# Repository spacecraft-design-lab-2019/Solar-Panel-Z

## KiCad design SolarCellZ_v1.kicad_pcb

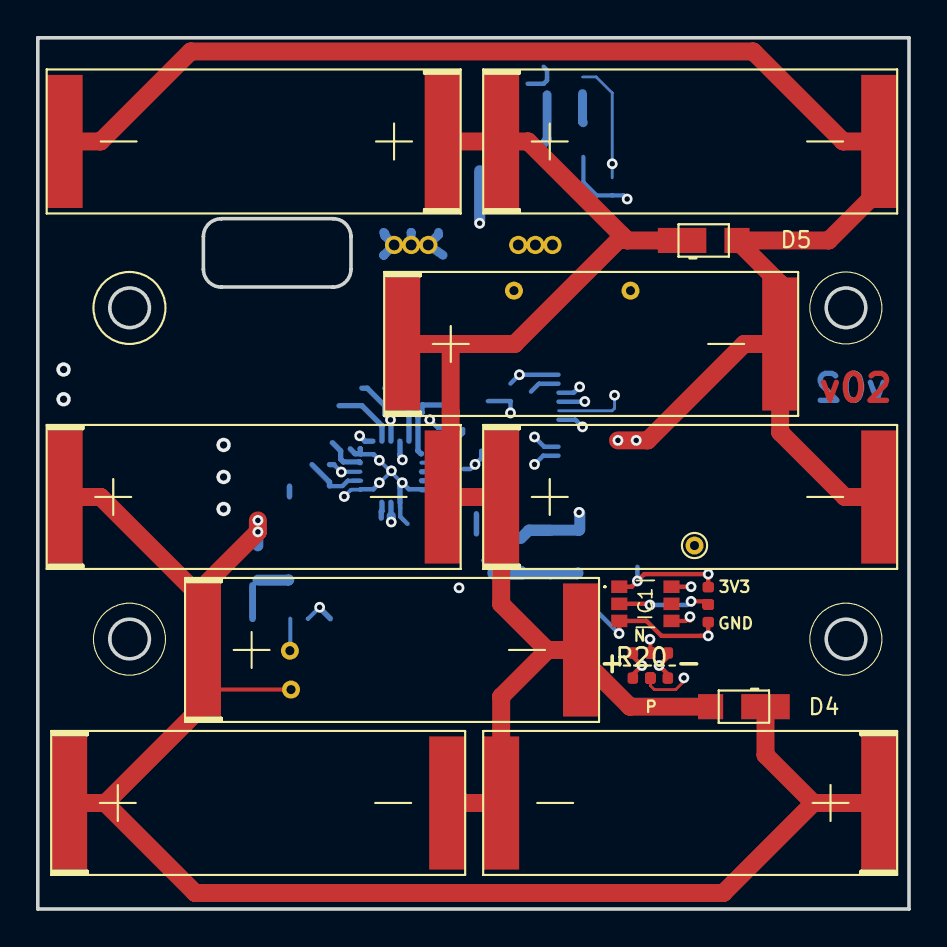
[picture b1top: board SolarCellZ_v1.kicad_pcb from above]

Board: 6 copper layers, 48.4 x 48.4 mm, 62 parts (0 on the bottom side), 31 nets.

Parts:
C1: 1.0uF; C_0402_1005Metric
C2, C5, C9, C10, C13: 0.1uF; C_0402_1005Metric
C3, C8: 4.7uF; C_0402_1005Metric
C4: 10nF; C_0402_1005Metric
C6, C11, C12, C14: 100uF; C_0603_1608Metric
C7: 22uF; C_0402_1005Metric
D1: SDM20U40-7; SOD523
D2, D3: MSS1P4-M3_89A; MICROSMP
D4, D5: SBDiode; SB Diode
IC1: TSL2561
J1: XF2M-1015-1A
JP1: Jumper; Burn-Wire-Rotated
L1: 22uH-LPS4018-223MR; LPS4018
L2: 10uH-LPS4018-103MR; LPS4018
Q1: IRLML2803; SOT-23
R1, R2, R12, R13, R14, R15, R16, R17, R18, R20, R21, R22: 0; R_0402_1005Metric
R3: 10k; R_0402_1005Metric
R4: 4.7k; R_0402_1005Metric
R5: 7.32M; R_0402_1005Metric
R6: 5.62M; R_0402_1005Metric
R7: 374K; R_0402_1005Metric
R8, R10: 8.25M; R_0402_1005Metric
R9: 4.53M; R_0402_1005Metric
R11: 4.75M; R_0402_1005Metric
R19: 100k; R_0402_1005Metric
SC1, SC2, SC3, SC4, SC5, SC6, SC7, SC8: SolarCell; KXOB25-05X3F
TP1, TP2, TP3, TP4, TP5: TP; TestPoint_THTPad_D1.0mm_Drill0.5mm
U1: NDS8434
U2: Value; QFN50P350X350X100-21N-D

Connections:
+3V3: C5.2, C13.1, C14.1, D2.1, IC1.1, J1.6, R12.2, TP3.1
/VBAT: C6.1, R17.2, U2.18
/VBURN: JP1.1, JP1.10, JP1.100, U1.5, U1.6, U1.7, U1.8
/coil: R2.2, R20.1, R21.2, R22.1
BATT_N: J1.2, R18.1
BATT_P: J1.1, R17.1, R19.2, TP5.1, U1.1, U1.2, U1.3
BURN1: J1.5, R3.1, R4.2, TP4.1
COIL_N: J1.9, R21.1, R22.2
COIL_P: J1.10, R2.1, R20.2
GND: C1.2, C2.2, C3.2, C4.2, C5.1, C6.2, C7.2, C8.2, C9.2, C10.2, C11.2, C12.2, C13.2, C14.2, D1.A, D5.2, IC1.3, J1.7, J1.8, JP1.2, JP1.20, JP1.200, Q1.2, R3.2, R6.1, R9.1, R11.1, R13.1, R15.1, R18.2, SC5.2, SC6.2, SC7.2, SC8.2, TP2.1, U2.1, U2.5, U2.9, U2.15, U2.17, U2.21
unnamed: C4.1, U2.4
unnamed: C7.1, C10.1, C12.1, D2.2, L2.2, U2.14
unnamed: C8.1, C9.1, C11.1, R16.1, U2.19
unnamed: D4.2, D5.1, SC1.2, SC2.2, SC3.2, SC4.2, SC5.1, SC6.1, SC7.1, SC8.1
unnamed: IC1.2, R12.1, R13.2
unnamed: L1.2, U2.20
unnamed: L2.1, U2.16
unnamed: Q1.1, R4.1
unnamed: Q1.3, R19.1, U1.4
unnamed: R5.1, R6.2, U2.7
unnamed: R7.1, R8.2, U2.10
unnamed: R8.1, R9.2, U2.11
unnamed: R10.1, R11.2, U2.12
unnamed: R5.2, R7.2, R10.2, U2.8
unnamed: R14.1, R15.2, R16.2, U2.3
SCL1: IC1.4, J1.4
SDA1: IC1.6, J1.3
SOLAR_OUT: D3.2, D4.1, SC1.1, SC2.1, SC3.1, SC4.1, TP1.1
VBAT_OK: R1.1, U2.13
VOUT_EN: C1.1, R1.2, U2.6
VSOLAR: C2.1, C3.1, D1.C, D3.1, L1.1, R14.2, U2.2

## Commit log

2019-10-23 Updated the mounting holes and cell arrangement
    Still working with structures on the location of the USB hole
2019-10-24 Added USB hole and other circuit components
2019-10-24 Added the first layer of the magnetorquer
2019-10-24 Finished Magnetorquer on Z board
2019-10-24 Reformatted Y+ board in new doc location.
2019-10-25 Cleaned up the Magnetorquer and added labels
2019-10-25 X and Z panels are ready
2019-10-26 zipped fabrication files for all but +Y
2019-10-26 JLCPCB fab output
2019-10-26 adding interactive BOMs for +/-X,-Y,+-Z
2019-10-26 Fixed nets again. Added proper mounting holes and pads for those mounting holes.
2019-10-28 generating 3D CAD
2019-11-01 stencil outputs
2019-12-10 Fixed floating via, extended pads, and added flatflex labels
2019-12-20 v01 order + repo overhaul
2020-02-10 fixed schematic / pcb mismatch
2020-02-26 fixed missing 3D models, exported STEP
2020-02-28 Modified magnetorquer coils
2020-02-29 design review and generated gerbers
2020-03-01 added fiducials, regenerated 3d model and gerbers
